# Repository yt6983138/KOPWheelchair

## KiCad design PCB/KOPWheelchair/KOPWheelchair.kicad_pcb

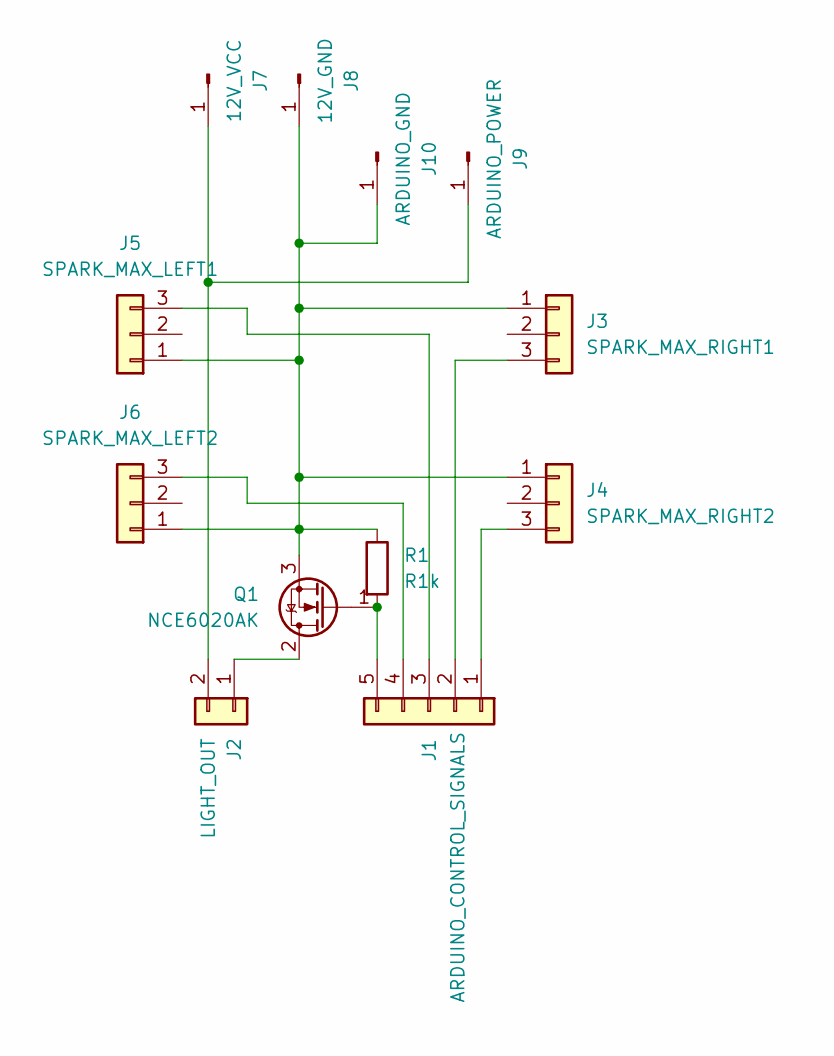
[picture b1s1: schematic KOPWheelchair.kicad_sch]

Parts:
J1: ARDUINO_CONTROL_SIGNALS; JST_XH_B5B-XH-A_1x05_P2.50mm_Vertical
J2: LIGHT_OUT; JST_XH_B2B-XH-A_1x02_P2.50mm_Vertical
J3: SPARK_MAX_RIGHT1; JST_XH_B3B-XH-A_1x03_P2.50mm_Vertical
J4: SPARK_MAX_RIGHT2; JST_XH_B3B-XH-A_1x03_P2.50mm_Vertical
J5: SPARK_MAX_LEFT1; JST_XH_B3B-XH-A_1x03_P2.50mm_Vertical
J6: SPARK_MAX_LEFT2; JST_XH_B3B-XH-A_1x03_P2.50mm_Vertical
J7: 12V_VCC; SolderWire-0.75sqmm_1x01_D1.25mm_OD2.3mm
J8: 12V_GND; SolderWire-0.75sqmm_1x01_D1.25mm_OD2.3mm
J9: ARDUINO_POWER; SolderWire-0.75sqmm_1x01_D1.25mm_OD2.3mm
J10: ARDUINO_GND; SolderWire-0.75sqmm_1x01_D1.25mm_OD2.3mm
Q1: NCE6020AK; TO-252-3_TabPin2
R1: R1k; R_Axial_DIN0207_L6.3mm_D2.5mm_P7.62mm_Horizontal

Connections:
unnamed: J1.1, J4.3
unnamed: J1.2, J3.3
unnamed: J1.3, J5.3
unnamed: J1.4, J6.3
unnamed: J1.5, Q1.1 (G), R1.2
unnamed: J2.1, Q1.2 (D)
unnamed: J2.2, J7.1, J9.1
unnamed: J3.1, J4.1, J5.1, J6.1, J8.1, J10.1, Q1.3 (S), R1.1

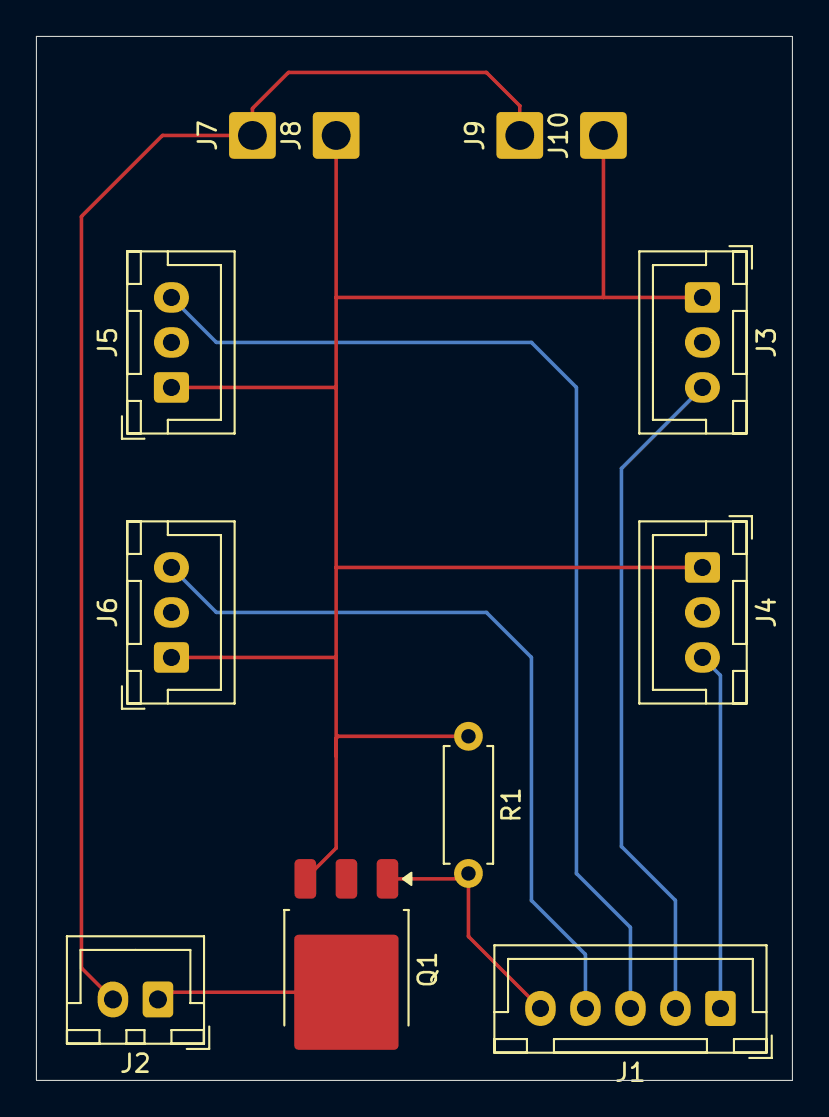
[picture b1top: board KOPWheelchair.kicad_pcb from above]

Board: 2 copper layers, 42.0 x 58.0 mm, 12 parts (0 on the bottom side), 8 nets.

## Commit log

2025-03-28 Add .gitattributes, .gitignore, README.md, and LICENSE.txt.
2025-03-28 Add project files.
2025-03-28 Joystick test
2025-03-28 Joystick test #2
2025-04-24 more update
2025-04-26 update at school
2026-05-12 Some refactor
2026-05-22 Fix after testing
